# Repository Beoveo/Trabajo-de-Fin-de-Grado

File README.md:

# Trabajo-de-Fin-de-Grado
Este es nuestro diseño hardware para el TFG titulado: Diseño de un sistema HW para evaluar el consumo de potencia de memorias SRAM con ECC. 

This is our hardware design from our BsC thesis: Design of a hardware system for evaluating power consumption of SRAM memories with ECC.

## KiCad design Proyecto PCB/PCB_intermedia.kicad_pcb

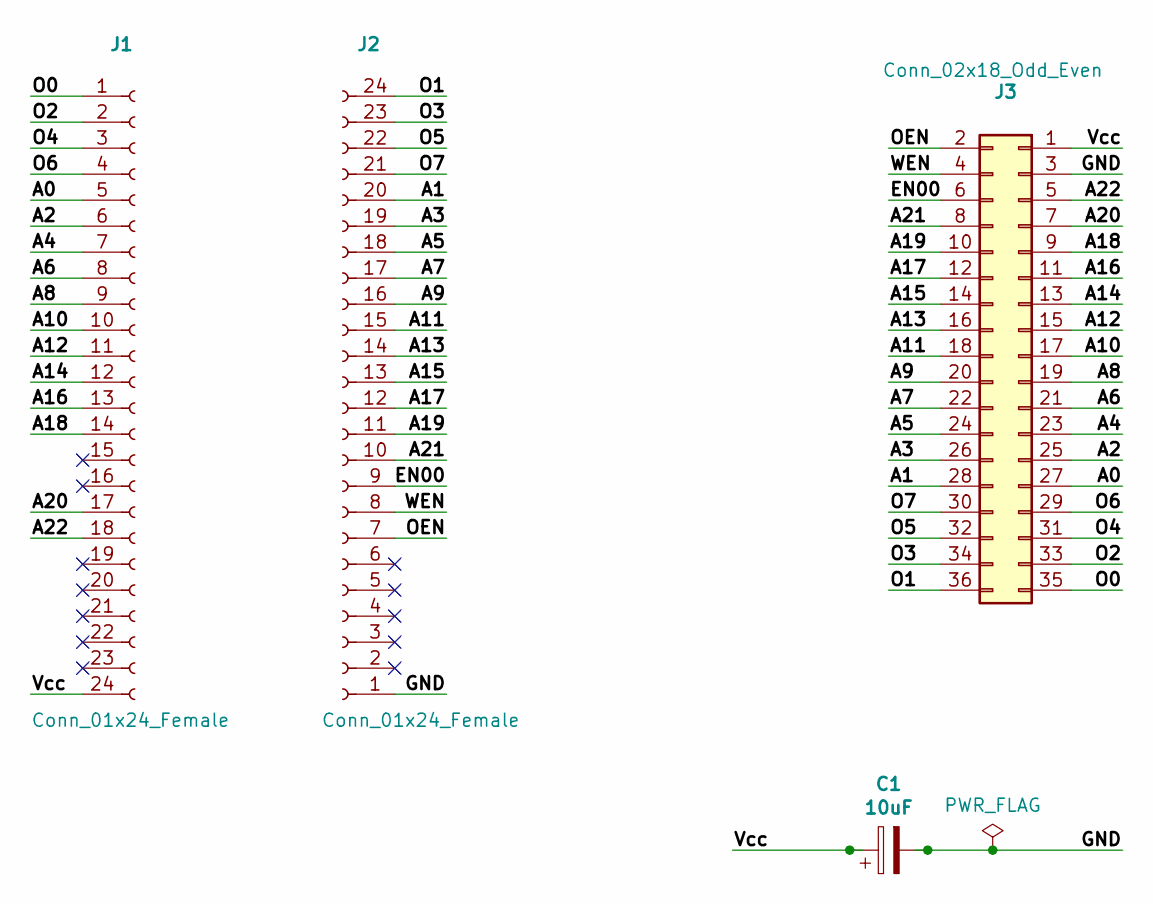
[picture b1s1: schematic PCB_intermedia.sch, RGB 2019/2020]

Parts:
C1: 10uF; C_Radial_D4.0mm_H5.0mm_P1.50mm
J1, J2: Conn_01x24_Female; PinSocket_1x24_P2.54mm_Vertical
J3: Conn_02x18_Odd_Even; PinHeader_2x18_P2.54mm_Vertical

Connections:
/A0: J1.5, J3.27
/A1: J2.20, J3.28
/A2: J1.6, J3.25
/A3: J2.19, J3.26
/A4: J1.7, J3.23
/A5: J2.18, J3.24
/A6: J1.8, J3.21
/A7: J2.17, J3.22
/A8: J1.9, J3.19
/A9: J2.16, J3.20
/A10: J1.10, J3.17
/A11: J2.15, J3.18
/A12: J1.11, J3.15
/A13: J2.14, J3.16
/A14: J1.12, J3.13
/A15: J2.13, J3.14
/A16: J1.13, J3.11
/A17: J2.12, J3.12
/A18: J1.14, J3.9
/A19: J2.11, J3.10
/A20: J1.17, J3.7
/A21: J2.10, J3.8
/A22: J1.18, J3.5
/EN00: J2.9, J3.6
/GND: C1.2, J2.1, J3.3
/O0: J1.1, J3.35
/O1: J2.24, J3.36
/O2: J1.2, J3.33
/O3: J2.23, J3.34
/O4: J1.3, J3.31
/O5: J2.22, J3.32
/O6: J1.4, J3.29
/O7: J2.21, J3.30
/OEN: J2.7, J3.2
/Vcc: C1.1, J1.24, J3.1
/WEN: J2.8, J3.4

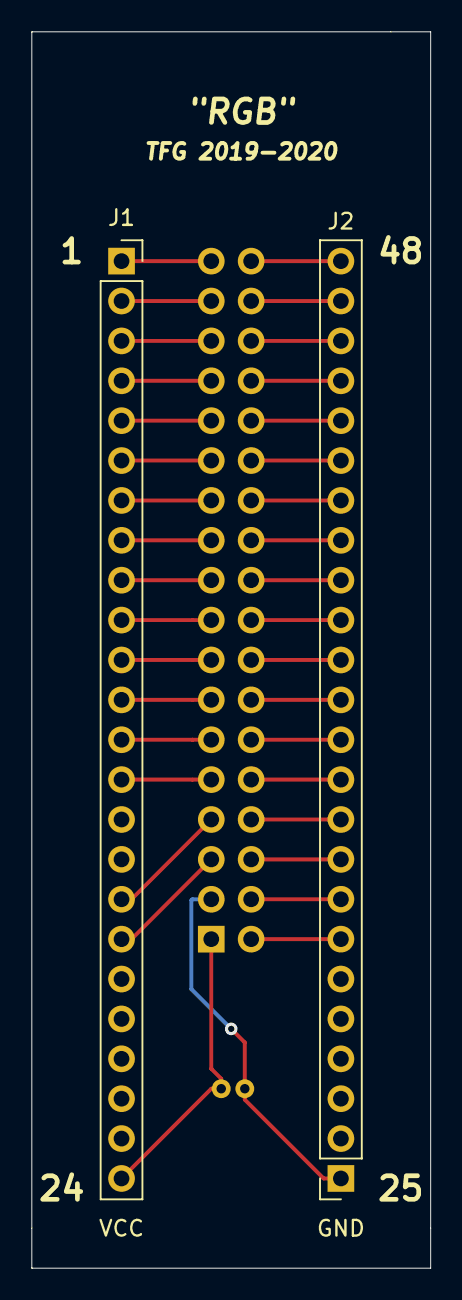
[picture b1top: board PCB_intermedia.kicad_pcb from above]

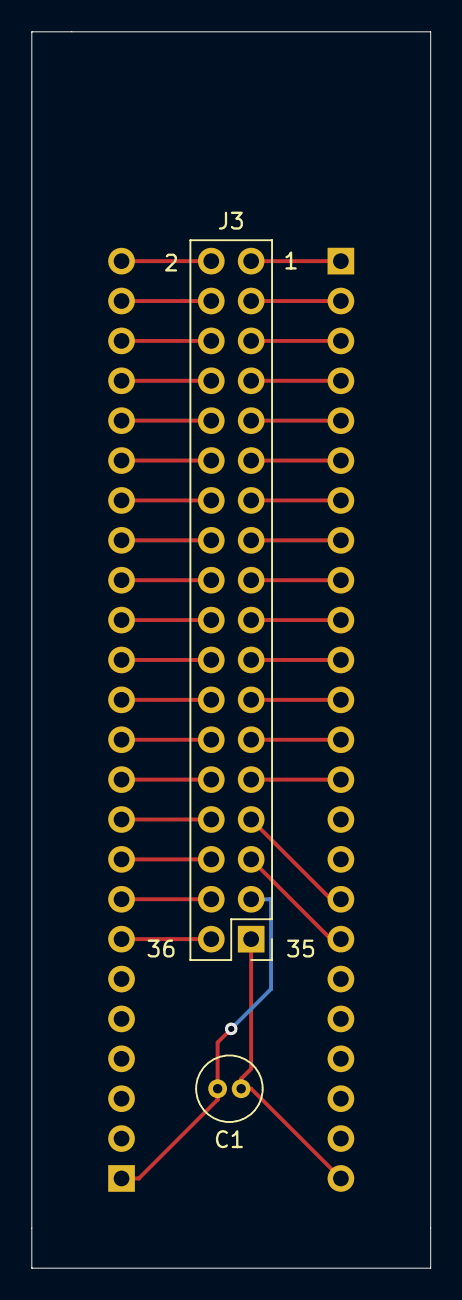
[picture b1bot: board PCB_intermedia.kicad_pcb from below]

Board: 2 copper layers, 25.4 x 78.7 mm, 4 parts (2 on the bottom side), 36 nets.

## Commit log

2020-09-18 Fichero de pines
2021-01-19 Creating a new folder
2021-01-19 change to a new path
2021-01-19 Create new folder for PCB files
2021-01-19 Final PCB with gerber files generated
2021-01-19 Final hardware design
